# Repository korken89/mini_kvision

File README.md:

# Mini KVision

Playing with the idea of a small KVision board.

This repository is a scratch pad / WIP.

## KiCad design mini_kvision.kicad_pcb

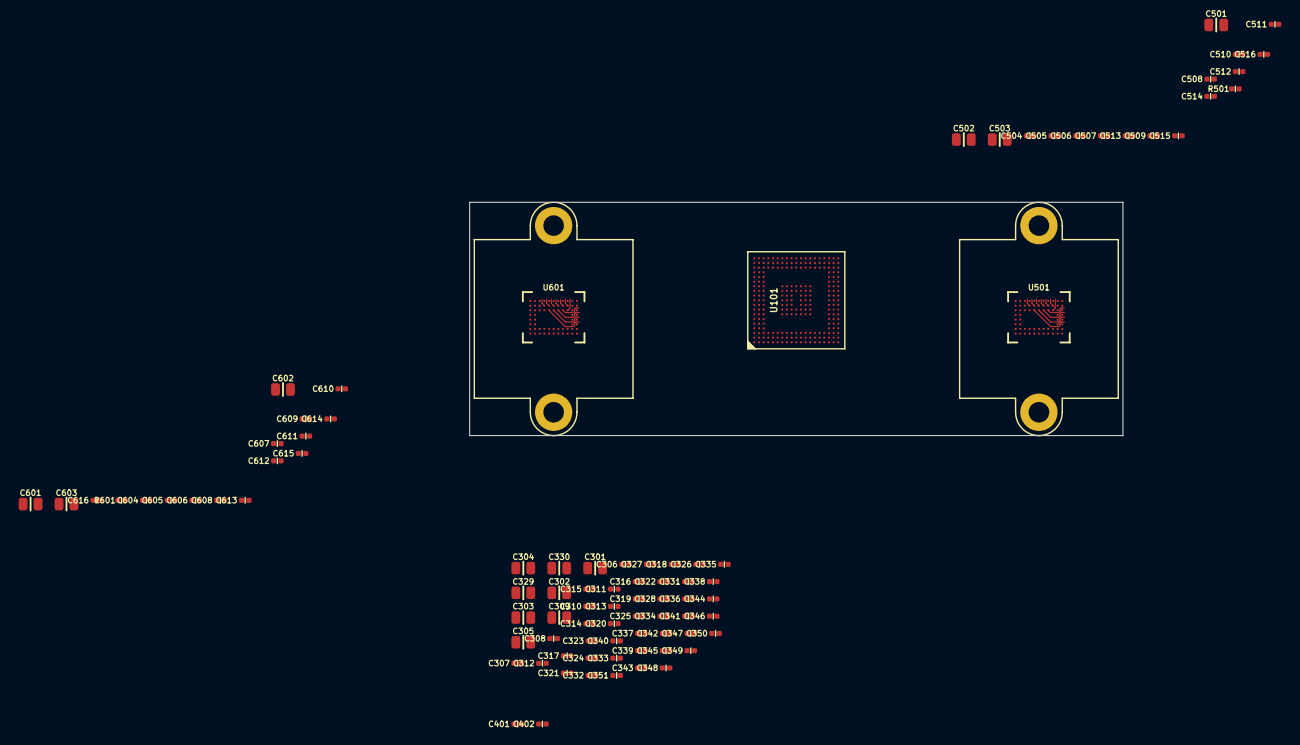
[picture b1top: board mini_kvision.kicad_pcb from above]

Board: 6 copper layers, 92 parts (0 on the bottom side), 19 nets.

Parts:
C301, C302, C303, C304, C305, C309, C329, C330, C501, C502, C503, C601, C602, C603: 47u; C_0805
C306, C307, C308, C310, C311, C312, C313, C316, C318, C321, C336, C337, C513, C613: 4.7u; C_0402
C314, C315, C317, C319, C320, C322, C323, C324, C325, C326, C327, C328, C331, C332, C333, C334, C335, C338, C339, C340, C341, C342, C343, C344, C345, C346, C347, C348, C349, C350, C351, C401, C402, C504, C505, C506, C507, C508, C509, C510, C511, C512, C514, C515, C516, C604, C605, C606, C607, C608, C609, C610, C611, C612, C614, C615, C616: 0.1u; C_0402
LH501, LH601: lens_holder; m12_20mm
R501, R601: 47k; R_0402
U101: XC7A15T-CPG236; CPG236_0.23mm
U501, U601: PYTHON480

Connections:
/Camera 1/1V8: C502.1, C505.1, C508.1, C511.1, U501.A2, U501.A10, U501.H9
/Camera 1/3V3: C501.1, C504.1, C507.1, C510.1, C514.1, C515.1, C516.1, U501.B1, U501.F11, U501.G3, U501.H10, U501.H11
/Camera 1/BIAS: R501.1, U501.E1
/Camera 1/VPIX: C503.1, C506.1, C509.1, C512.1, U501.A1, U501.B6, U501.B10
/Camera 1/VREF: C513.1, U501.H6
/Camera 2/1V8: C602.1, C605.1, C608.1, C611.1, U601.A2, U601.A10, U601.H9
/Camera 2/3V3: C601.1, C604.1, C607.1, C610.1, C614.1, C615.1, C616.1, U601.B1, U601.F11, U601.G3, U601.H10, U601.H11
/Camera 2/BIAS: R601.1, U601.E1
/Camera 2/VPIX: C603.1, C606.1, C609.1, C612.1, U601.A1, U601.B6, U601.B10
/Camera 2/VREF: C613.1, U601.H6
/Config/VCCO_0: C401.1, C402.1, U101.G12, U101.V9
/Power/VCCAUX: C329.1, C336.1, C343.1, C350.1, U101.H13, U101.J13
/Power/VCCBRAM: C330.1, C337.1, C344.1, C351.1, U101.M11, U101.N11
/Power/VCCINT: C305.1, C309.1, C313.1, C318.1, C323.1, C328.1, C335.1, C342.1, C349.1, U101.G10, U101.H10, U101.J10, U101.L10, U101.M10, U101.N10
/VCCO_14: C301.1, C304.1, C308.1, C312.1, C317.1, C322.1, C327.1, C334.1, C341.1, C348.1, U101.F17, U101.K12, U101.K13, U101.L12, U101.L13, U101.M12, U101.M17, U101.R17, U101.U13
/VCCO_16: C316.1, C321.1, C326.1, C333.1, C340.1, C347.1, U101.B19, U101.C14, U101.C18, U101.G13
/VCCO_34: C302.1, C306.1, C310.1, C314.1, C319.1, C324.1, C331.1, C338.1, C345.1, U101.M8, U101.N7, U101.N8, U101.R1, U101.V1, U101.V6
/VCCO_35: C303.1, C307.1, C311.1, C315.1, C320.1, C325.1, C332.1, C339.1, C346.1, U101.H3, U101.J7, U101.K1, U101.K7, U101.L7, U101.M7
GND: C301.2, C302.2, C303.2, C304.2, C305.2, C306.2, C307.2, C308.2, C309.2, C310.2, C311.2, C312.2, C313.2, C314.2, C315.2, C316.2, C317.2, C318.2, C319.2, C320.2, C321.2, C322.2, C323.2, C324.2, C325.2, C326.2, C327.2, C328.2, C329.2, C330.2, C331.2, C332.2, C333.2, C334.2, C335.2, C336.2, C337.2, C338.2, C339.2, C340.2, C341.2, C342.2, C343.2, C344.2, C345.2, C346.2, C347.2, C348.2, C349.2, C350.2, C351.2, C401.2, C402.2, C501.2, C502.2, C503.2, C504.2, C505.2, C506.2, C507.2, C508.2, C509.2, C510.2, C511.2, C512.2, C513.2, C514.2, C515.2, C516.2, C601.2, C602.2, C603.2, C604.2, C605.2, C606.2, C607.2, C608.2, C609.2, C610.2, C611.2, C612.2, C613.2, C614.2, C615.2, C616.2, LH501.1, LH501.2, LH601.1, LH601.2, R501.2, R601.2, U101.A1, U101.A3, U101.A4, U101.A5, U101.A6, U101.A7, U101.A9, U101.A19, U101.B1, U101.B3, U101.B4, U101.B5, U101.B6, U101.B7, U101.B9, U101.B14, U101.C1, U101.C2, U101.C3, U101.C4, U101.C5, U101.C6, U101.C7, U101.C10, U101.C19, U101.D3, U101.E1, U101.E2, U101.E3, U101.E17, U101.F1, U101.F2, U101.F3, U101.F19, U101.G1, U101.G7, U101.G8, U101.G9, U101.G11, U101.H7, U101.H8, U101.H9, U101.H11, U101.H12, U101.H18, U101.J8, U101.J9, U101.J11, U101.J12, U101.K8, U101.L8, U101.L9, U101.L11, U101.L19, U101.M9, U101.M13, U101.N9, U101.N12, U101.N13, U101.P2, U101.T19, U101.U6, U101.U9, U101.V18, U101.W1, U101.W12, U501.A3, U501.A6, U501.A11, U501.B2, U501.B3, U501.C2, U501.D2, U501.E2, U501.G2, U501.G6, U501.G7, U501.G8, U501.G10, U501.G11, U501.H5, U501.H7, U501.H8, U601.A3, U601.A6, U601.A11, U601.B2, U601.B3, U601.C2, U601.D2, U601.E2, U601.G2, U601.G6, U601.G7, U601.G8, U601.G10, U601.G11, U601.H5, U601.H7, U601.H8
